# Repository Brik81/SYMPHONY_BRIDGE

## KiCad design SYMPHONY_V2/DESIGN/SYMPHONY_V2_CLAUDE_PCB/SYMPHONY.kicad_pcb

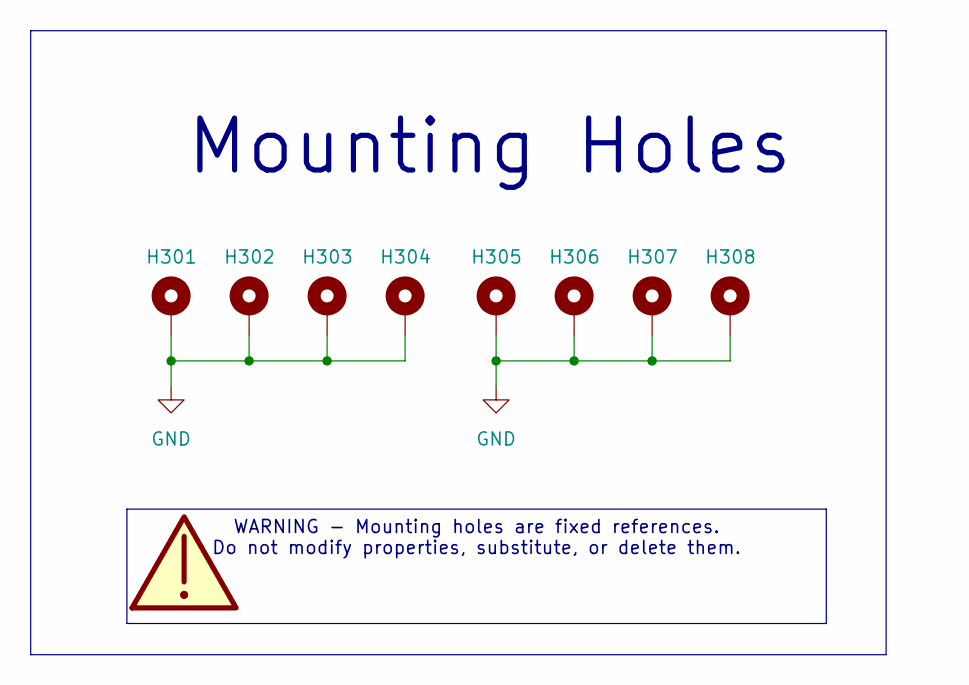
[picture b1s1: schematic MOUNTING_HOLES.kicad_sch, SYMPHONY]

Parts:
H301, H302, H303, H304, H305, H306, H307, H308: MountingHole_Pad; MountingHole_2.2mm_M2_DIN965_Pad

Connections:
GND: H301.1 (1_1), H302.1 (1_1), H303.1 (1_1), H304.1 (1_1), H305.1 (1_1), H306.1 (1_1), H307.1 (1_1), H308.1 (1_1); also elsewhere on the board

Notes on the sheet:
Mounting Holes
WARNING - Mounting holes are fixed references. Do not modify properties, substitute, or delete them.

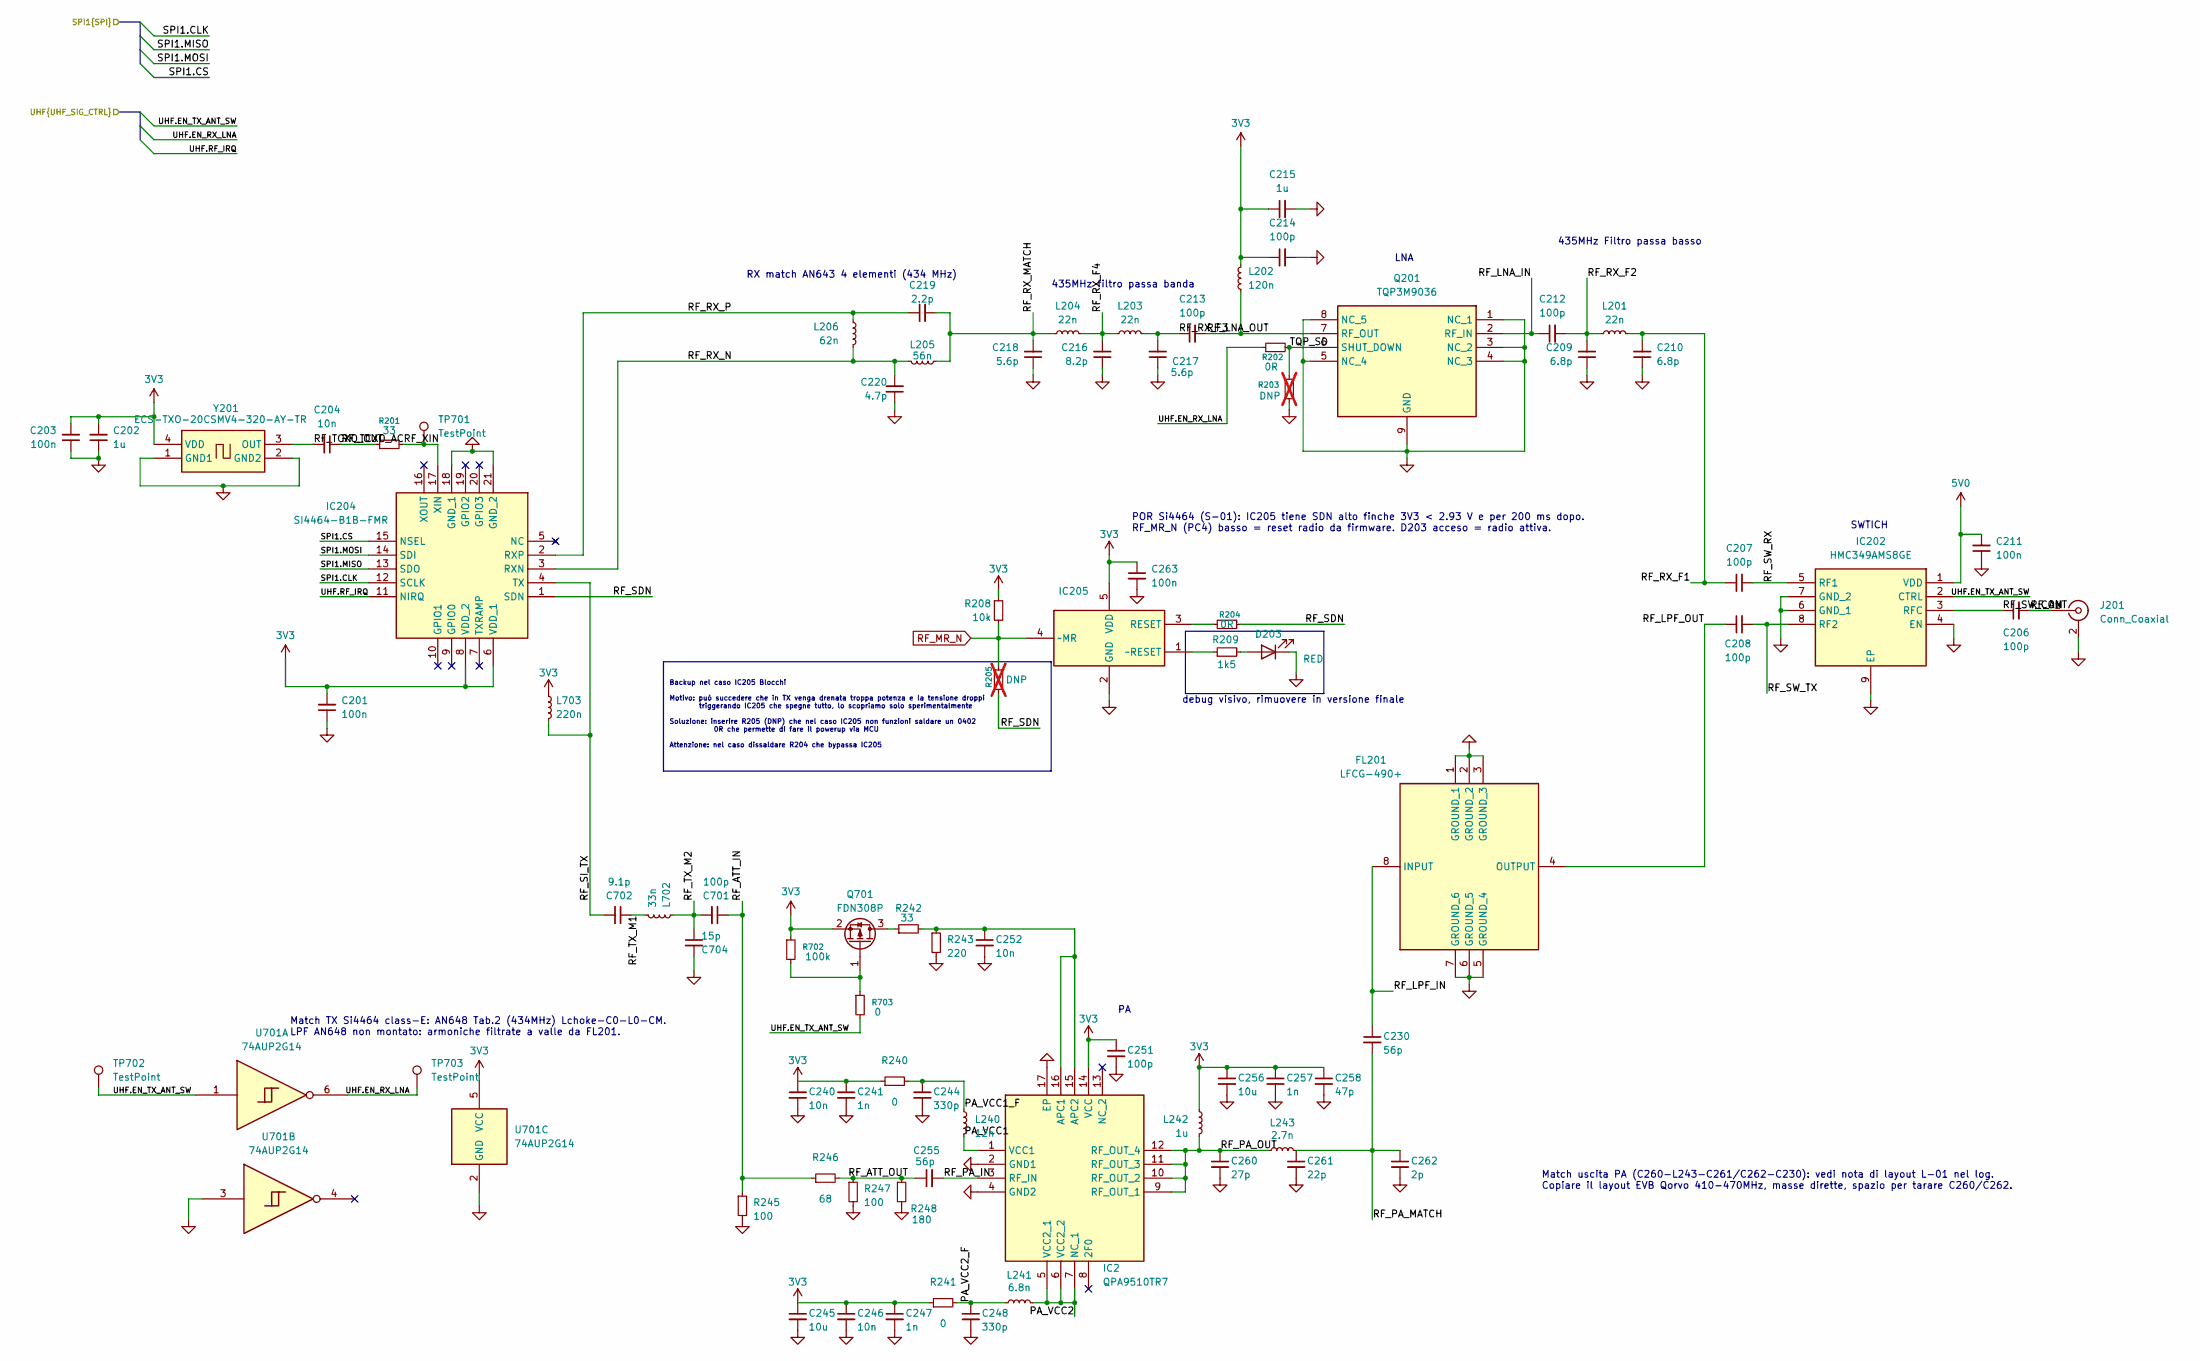
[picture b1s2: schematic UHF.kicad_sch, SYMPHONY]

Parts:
C201, C203, C211, C263: 100n; C_0402_1005Metric; JLCPCB Parts C77014
C202, C215: 1u; C_0402_1005Metric; JLCPCB Parts C77009
C204: 10n; C_0402_1005Metric; JLCPCB Parts C77013
C206, C207, C208, C212, C213, C701: 100p; C_0603_1608Metric; JLCPCB Parts C17308632
C209, C210: 6.8p; C_0805_2012Metric; JLCPCB Parts C464958
C214: 100p; C_0402_1005Metric; JLCPCB Parts C77177
C216: 8.2p; C_0805_2012Metric; JLCPCB Parts C668333
C217, C218: 5.6p; C_0603_1608Metric; JLCPCB Parts C2297617
C219: 2.2p; C_0603_1608Metric; JLCPCB Parts C2179335
C220: 4.7p; C_0805_2012Metric; JLCPCB Parts C5646702
C230, C255: 56p; C_0603_1608Metric; JLCPCB Parts C237591
C240, C246, C252: 10n; C_0402_1005Metric_Pad0.74x0.62mm_HandSolder; JLCPCB Parts C77013
C241, C247, C257: 1n; C_0402_1005Metric_Pad0.74x0.62mm_HandSolder; JLCPCB Parts C76947
C244, C248: 330p; C_0402_1005Metric_Pad0.74x0.62mm_HandSolder; JLCPCB Parts C76965
C245, C256: 10u; C_0805_2012Metric_Pad1.18x1.45mm_HandSolder; JLCPCB Parts C84416
C251: 100p; C_0402_1005Metric_Pad0.74x0.62mm_HandSolder; JLCPCB Parts C77177
C258: 47p; C_0402_1005Metric_Pad0.74x0.62mm_HandSolder; JLCPCB Parts C76970
C260: 27p; C_0603_1608Metric; JLCPCB Parts C2360423
C261: 22p; C_0402_1005Metric; JLCPCB Parts C882567
C262: 2p; C_0402_1005Metric; JLCPCB Parts C161316
C702: 9.1p; C_0402_1005Metric; JLCPCB Parts C497527
C704: 15p; C_0402_1005Metric; JLCPCB Parts C441742
D203: RED; LED_0402_1005Metric; JLCPCB Parts C130719
FL201: LFCG-490+; LFCG490; Mouser Part Number 139-LFCG-490+
IC2: QPA9510TR7; QFN50P300X300X90-17N-D; Manufacturer_Part_Number QPA9510TR7; JLCPCB Parts C52059849
IC202: HMC349AMS8GE; SOP65P490X110-9N; Mouser Part Number 584-HMC349AMS8GE
IC204: SI4464-B1B-FMR; QFN50P400X400X90-21N-D; Mouser Part Number 634-SI4464-B1X-FMR
IC205: TPS3825-33DBVR; SOT95P280X145-5N; Manufacturer_Part_Number TPS3825-33DBVR; JLCPCB Parts C473344
J201: Conn_Coaxial; MMCX_Molex_73415-0961_Horizontal_0.8mm-PCB; JLCPCB Parts C2999837
L201, L203, L204: 22n; L_0805_2012Metric; JLCPCB Parts C2042193
L202: 120n; L_0402_1005Metric_Pad0.77x0.64mm_HandSolder; JLCPCB Parts C113123
L205: 56n; L_0603_1608Metric; JLCPCB Parts C98079
L206: 62n; L_0603_1608Metric; JLCPCB Parts C162649
L240: 12n; L_0603_1608Metric_Pad1.05x0.95mm_HandSolder; JLCPCB Parts C98068
L241: 6.8n; L_0402_1005Metric_Pad0.77x0.64mm_HandSolder; JLCPCB Parts C882467
L242: 1u; L_Taiyo-Yuden_NR-20xx; Manufacturer_Part_Number NRS2012T1R0NGJV; Mouser Part Number 963-NRS2012T1R0NGJV
L243: 2.7n; L_0402_1005Metric; JLCPCB Parts C412269
L702: 33n; L_0805_2012Metric; JLCPCB Parts C1330869
L703: 220n; L_0603_1608Metric; JLCPCB Parts C2046586
Q201: TQP3M9036; SON50P200X200X95-9N-D; Mouser Part Number 772-TQP3M9036
Q701: FDN308P; SOT-23; JLCPCB Parts C7472857
R201: 33; R_0402_1005Metric; JLCPCB Parts C25105
R202, R204: 0R; R_0402_1005Metric; JLCPCB Parts C17168
R203: DNP; R_0402_1005Metric; JLCPCB Parts C71617; not fitted
R205: DNP; R_0402_1005Metric; JLCPCB Parts C17168; not fitted
R208: 10k; R_0402_1005Metric; JLCPCB Parts C71617
R209: 1k5; R_0402_1005Metric; JLCPCB Parts C25867
R240: 0; R_0402_1005Metric_Pad0.72x0.64mm_HandSolder; JLCPCB Parts C17168
R241: 0; R_0603_1608Metric_Pad0.98x0.95mm_HandSolder; JLCPCB Parts C21189
R242: 33; R_0402_1005Metric_Pad0.72x0.64mm_HandSolder; JLCPCB Parts C25105
R243: 220; R_0402_1005Metric_Pad0.72x0.64mm_HandSolder; JLCPCB Parts C25091
R245: 100; R_0603_1608Metric; JLCPCB Parts C22775
R246: 68; R_0603_1608Metric; JLCPCB Parts C27592
R247: 100; R_0402_1005Metric; JLCPCB Parts C25076
R248: 180; R_0402_1005Metric; JLCPCB Parts C38941
R702: 100k; R_0402_1005Metric; JLCPCB Parts C60491
R703: 0; R_0402_1005Metric; JLCPCB Parts C17168
TP701, TP702, TP703: TestPoint; TestPoint_Pad_D1.0mm
U701: 74AUP2G14; SOT-363_SC-70-6; JLCPCB Parts C526337
Y201: ECS-TXO-20CSMV4-320-AY-TR; ECSTXO20CSMV4320AYTR; Manufacturer_Part_Number ECS-TXO-20CSMV4-320-AY-TR; JLCPCB Parts C19858587

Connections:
3V3: C201.2, C202.2, C203.2, C214.1, C215.1, C240.1, C241.1, C245.1, C246.1, C247.1, C251.1, C256.1, C257.1, C258.1, C263.1, IC2.14 (VCC), IC204.6 (VDD_1), IC204.8 (VDD_2), IC205.5 (VDD), L202.2, L242.1, L703.1, Q701.2 (S), R208.1, R240.1, R241.1, R702.1, U701.5 (VCC), Y201.4 (VDD); also elsewhere on the board
5V0: C211.2, IC202.1 (VDD); also elsewhere on the board
/MCU/SPI1.CLK: IC204.12 (SCLK); also elsewhere on the board
/MCU/SPI1.CS: IC204.15 (NSEL); also elsewhere on the board
/MCU/SPI1.MISO: IC204.13 (SDO); also elsewhere on the board
/MCU/SPI1.MOSI: IC204.14 (SDI); also elsewhere on the board
/MCU/UHF.EN_RX_LNA: R202.1, TP703.1 (1_1), U701.6
/MCU/UHF.EN_TX_ANT_SW: IC202.2 (CTRL), R703.2, TP702.1 (1_1), U701.1; also elsewhere on the board
/MCU/UHF.RF_IRQ: IC204.11 (NIRQ); also elsewhere on the board
/UHF/PA_VCC1: IC2.1 (VCC1), L240.2
/UHF/PA_VCC1_F: C244.1, L240.1, R240.2
/UHF/PA_VCC2: IC2.5 (VCC2_1), IC2.6 (VCC2_2), IC2.7 (NC_1), L241.2
/UHF/PA_VCC2_F: C248.1, L241.1, R241.2
/UHF/RF_ANT: C206.2, J201.1 (In)
/UHF/RF_ATT_IN: C701.1, R245.1, R246.1
/UHF/RF_ATT_OUT: C255.1, R246.2, R247.1, R248.1
/UHF/RF_LNA_IN: C212.1, Q201.2 (RF_IN)
/UHF/RF_LNA_OUT: C213.2, L202.1, Q201.7 (RF_OUT)
/UHF/RF_LPF_IN: C230.1, FL201.8 (INPUT)
/UHF/RF_LPF_OUT: C208.1, FL201.4 (OUTPUT)
/UHF/RF_PA_IN: C255.2, IC2.3 (RF_IN)
/UHF/RF_PA_MATCH: C230.2, C261.1, C262.1, L243.2
/UHF/RF_PA_OUT: C260.1, IC2.9 (RF_OUT_1), IC2.10 (RF_OUT_2), IC2.11 (RF_OUT_3), IC2.12 (RF_OUT_4), L242.2, L243.1
/UHF/RF_RX_F1: C207.1, C210.2, L201.2
/UHF/RF_RX_F2: C209.2, C212.2, L201.1
/UHF/RF_RX_F3: C213.1, C217.2, L203.2
/UHF/RF_RX_F4: C216.2, L203.1, L204.2
/UHF/RF_RX_MATCH: C218.2, C219.2, L204.1, L205.2
/UHF/RF_RX_N: C220.2, IC204.3 (RXN), L205.1, L206.2
/UHF/RF_RX_P: C219.1, IC204.2 (RXP), L206.1
/UHF/RF_SDN: IC204.1 (SDN), R204.1, R205.2
/UHF/RF_SI_TX: C702.2, IC204.4 (TX), L703.2
/UHF/RF_SW_COM: C206.1, IC202.3 (RFC)
/UHF/RF_SW_RX: C207.2, IC202.5 (RF1)
/UHF/RF_SW_TX: C208.2, IC202.8 (RF2)
/UHF/RF_TCXO_AC: C204.1, R201.1
/UHF/RF_TCXO_OUT: C204.2, Y201.3 (OUT)
/UHF/RF_TX_M1: C702.1, L702.1
/UHF/RF_TX_M2: C701.2, C704.1, L702.2
/UHF/RF_XIN: IC204.17 (XIN), R201.2, TP701.1 (1_1)
/UHF/TQP_SD: Q201.6 (SHUT_DOWN), R202.2, R203.1
GND: C201.1, C202.1, C203.1, C209.1, C210.1, C211.1, C214.2, C215.2, C216.1, C217.1, C218.1, C220.1, C240.2, C241.2, C244.2, C245.2, C246.2, C247.2, C248.2, C251.2, C252.2, C256.2, C257.2, C258.2, C260.2, C261.2, C262.2, C263.2, C704.2, D203.1 (K), FL201.1 (GROUND_1), FL201.2 (GROUND_2), FL201.3 (GROUND_3), FL201.5 (GROUND_4), FL201.6 (GROUND_5), FL201.7 (GROUND_6), IC2.2 (GND1), IC2.4 (GND2), IC2.17 (EP), IC202.4 (EN), IC202.6 (GND_1), IC202.7 (GND_2), IC202.9 (EP), IC204.18 (GND_1), IC204.21 (GND_2), IC205.2 (GND), J201.2 (Ext), Q201.1 (NC_1), Q201.3 (NC_2), Q201.4 (NC_3), Q201.5 (NC_4), Q201.8 (NC_5), Q201.9 (GND), R203.2, R243.2, R245.2, R247.2, R248.2, U701.2 (GND), U701.3, Y201.1 (GND1), Y201.2 (GND2); also elsewhere on the board
unnamed: D203.2 (A), R209.2
unnamed: C252.1, IC2.15 (APC2), IC2.16 (APC1), R242.2, R243.1
unnamed: IC205.3 (RESET), R204.2
unnamed: IC205.1 (~RESET), R209.1
unnamed: Q701.3 (D), R242.1
unnamed: Q701.1 (G), R702.2, R703.1
RF_MR_N: IC205.4 (~MR), R205.1, R208.2; also elsewhere on the board

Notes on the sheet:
435MHz Filtro passa basso
Match TX Si4464 class-E: AN648 Tab.2 (434MHz) Lchoke-C0-L0-CM. LPF AN648 non montato: armoniche filtrate a valle da FL201.
POR Si4464 (S-01): IC205 tiene SDN alto finche 3V3 < 2.93 V e per 200 ms dopo. RF_MR_N (PC4) basso = reset radio da firmware. D203 acceso = radio attiva.
debug visivo, rimuovere in versione finale
LNA
Backup nel caso IC205 Blocchi Motivo: può succedere che in TX venga drenata troppa potenza e la tensione droppi triggerando IC205 che spegne tutto, lo scopriamo solo sperimentalmente Soluzione: inserire R205 (DNP) che nel caso IC205 non funzioni saldare un 0402 0R che permette di fare il powerup vi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
435MHz filtro passa banda
RX match AN643 4 elementi (434 MHz)
SWTICH
Match uscita PA (C260-L243-C261/C262-C230): vedi nota di layout L-01 nel log. Copiare il layout EVB Qorvo 410-470MHz, masse dirette, spazio per tarare C260/C262.

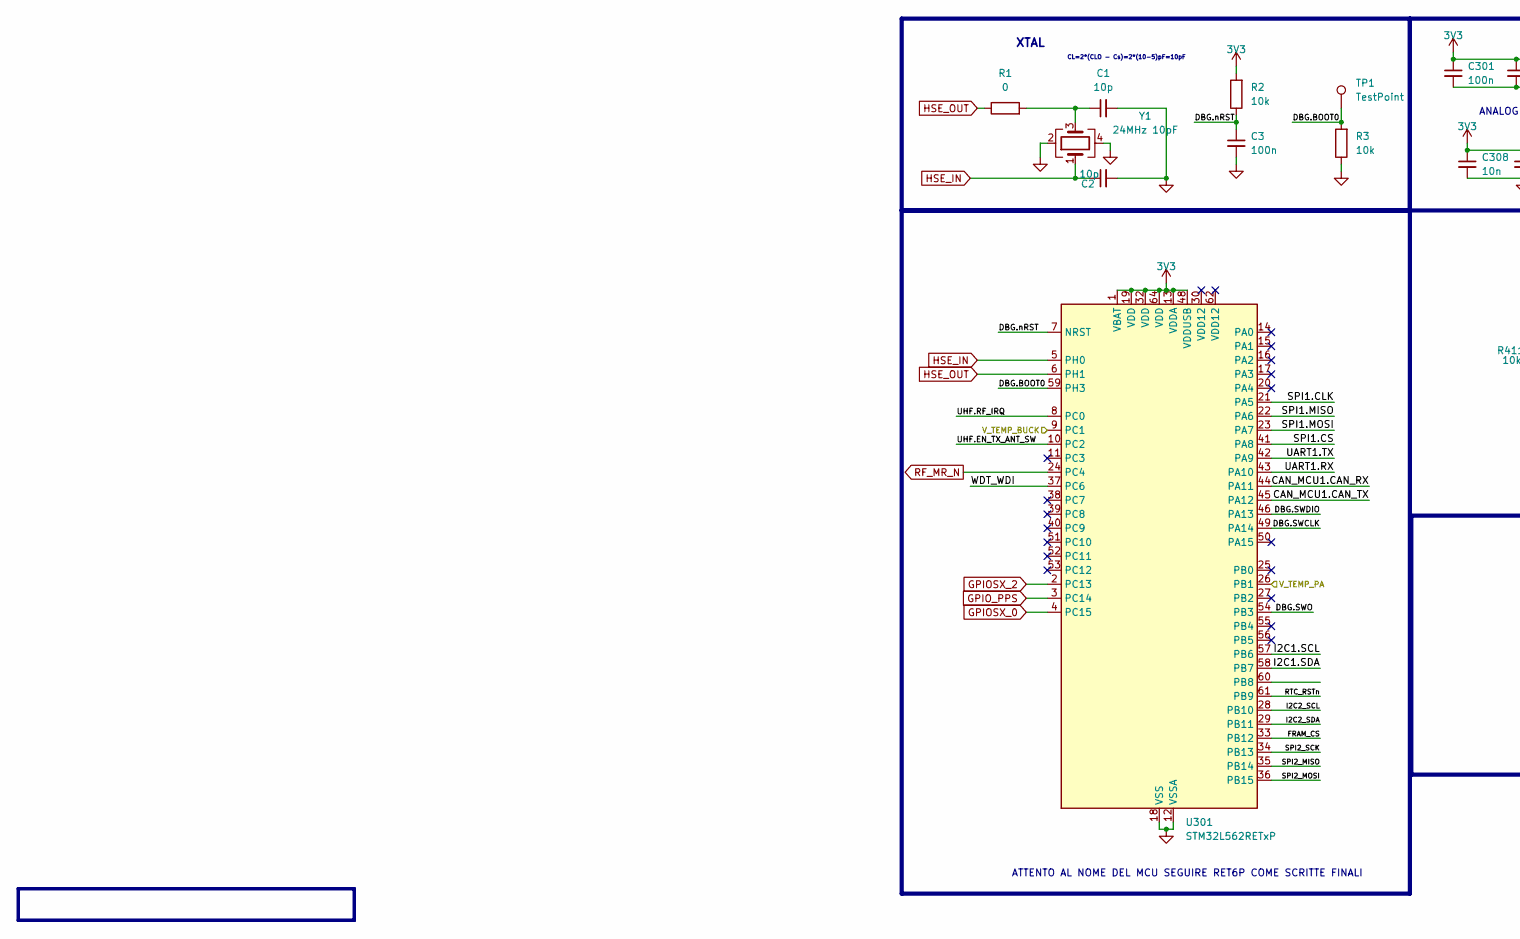
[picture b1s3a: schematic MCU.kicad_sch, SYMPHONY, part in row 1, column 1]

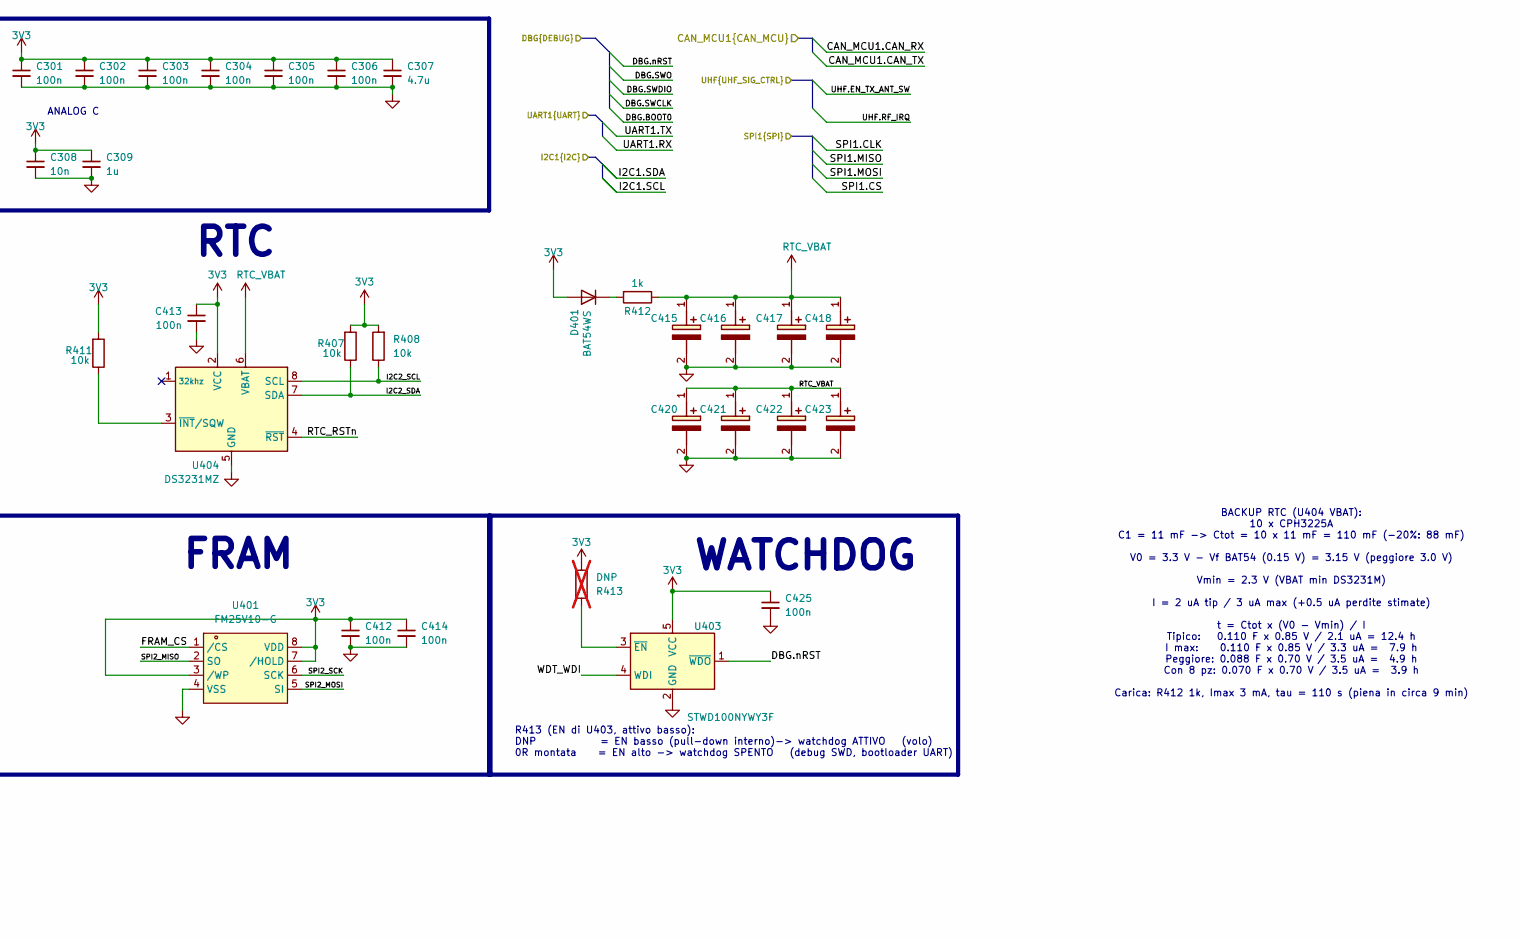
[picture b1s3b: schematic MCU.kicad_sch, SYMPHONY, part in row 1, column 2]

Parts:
C1, C2: 10p; C_0402_1005Metric; JLCPCB Parts C76946
C3, C425: 100n; C_0402_1005Metric; JLCPCB Parts C1525
C301, C302, C303, C304, C305, C306, C412, C413, C414: 100n; C_0402_1005Metric_Pad0.74x0.62mm_HandSolder; JLCPCB Parts C1525
C307: 4.7u; C_0603_1608Metric_Pad1.08x0.95mm_HandSolder; JLCPCB Parts C19666
C308: 10n; C_0402_1005Metric_Pad0.74x0.62mm_HandSolder; JLCPCB Parts C1524
C309: 1u; C_0402_1005Metric_Pad0.74x0.62mm_HandSolder; JLCPCB Parts C14445
C415, C416, C417, C418, C420, C421, C422, C423: CPH3225A; Mouser Part Number 628-CPH3225A
D401: BAT54WS; D_SOD-323; JLCPCB Parts C124205
R1: 0; R_0402_1005Metric_Pad0.72x0.64mm_HandSolder; JLCPCB Parts C17168
R2, R3, R407, R408, R411: 10k; R_0402_1005Metric_Pad0.72x0.64mm_HandSolder; JLCPCB Parts C71617
R412: 1k; R_0402_1005Metric; JLCPCB Parts C11702
R413: DNP; R_0402_1005Metric; JLCPCB Parts C17168; not fitted
TP1: TestPoint; TestPoint_Pad_D1.0mm
U301: STM32L562RETxP; LQFP-64_10x10mm_P0.5mm; JLCPCB Parts C1236664
U401: FM25V10-G; SOIC127P602X173-8N; JLCPCB Parts C44173
U403: STWD100NYWY3F; SOT95P280X145-5N; Manufacturer_Part_Number STWD100NYWY3F; JLCPCB Parts C46043
U404: DS3231MZ; SOIC-8_3.9x4.9mm_P1.27mm; JLCPCB Parts C107410
Y1: 24MHz 10pF; Crystal_SMD_3225-4Pin_3.2x2.5mm; JLCPCB Parts C70583

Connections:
3V3: C301.1, C302.1, C303.1, C304.1, C305.1, C306.1, C307.1, C308.1, C309.1, C412.1, C413.1, C414.1, C425.1, D401.2 (A), R2.2, R407.2, R408.2, R411.2, R413.2, U301.1 (VBAT), U301.13 (VDDA), U301.19 (VDD), U301.32 (VDD), U301.48 (VDDUSB), U301.64 (VDD), U401.3 (/WP), U401.7 (/HOLD), U401.8 (VDD), U403.5 (VCC), U404.2 (VCC); also elsewhere on the board
/IF/CAN_MCU1.CAN_RX: U301.44 (PA11); also elsewhere on the board
/IF/CAN_MCU1.CAN_TX: U301.45 (PA12); also elsewhere on the board
/IF/DBG.BOOT0: R3.2, TP1.1 (1_1), U301.59 (PH3)
/IF/DBG.SWCLK: U301.49 (PA14); also elsewhere on the board
/IF/DBG.SWDIO: U301.46 (PA13); also elsewhere on the board
/IF/DBG.SWO: U301.54 (PB3); also elsewhere on the board
/IF/DBG.nRST: C3.1, R2.1, U301.7 (NRST), U403.1 (~WDO); also elsewhere on the board
/IF/I2C1.SCL: U301.57 (PB6); also elsewhere on the board
/IF/I2C1.SDA: U301.58 (PB7); also elsewhere on the board
/IF/UART1.RX: U301.43 (PA10); also elsewhere on the board
/IF/UART1.TX: U301.42 (PA9); also elsewhere on the board
/MCU/FRAM_CS: U301.33 (PB12), U401.1 (/CS)
/MCU/I2C2_SCL: R408.1, U301.28 (PB10), U404.8 (SCL)
/MCU/I2C2_SDA: R407.1, U301.29 (PB11), U404.7 (SDA)
/MCU/RTC_RSTn: U301.61 (PB9), U404.4 (~RST)
/MCU/SPI1.CLK: U301.21 (PA5); also elsewhere on the board
/MCU/SPI1.CS: U301.41 (PA8); also elsewhere on the board
/MCU/SPI1.MISO: U301.22 (PA6); also elsewhere on the board
/MCU/SPI1.MOSI: U301.23 (PA7); also elsewhere on the board
/MCU/SPI2_MISO: U301.35 (PB14), U401.2 (SO)
/MCU/SPI2_MOSI: U301.36 (PB15), U401.5 (SI)
/MCU/SPI2_SCK: U301.34 (PB13), U401.6 (SCK)
/MCU/UHF.EN_TX_ANT_SW: U301.10 (PC2); also elsewhere on the board
/MCU/UHF.RF_IRQ: U301.8 (PC0); also elsewhere on the board
/MCU/V_TEMP_BUCK: U301.9 (PC1); also elsewhere on the board
/MCU/V_TEMP_PA: U301.26 (PB1); also elsewhere on the board
/MCU/WDT_WDI: U301.37 (PC6), U403.4 (WDI)
GND: C1.2, C2.2, C3.2, C301.2, C302.2, C303.2, C304.2, C305.2, C306.2, C307.2, C308.2, C309.2, C412.2, C413.2, C414.2, C415.2 (-), C416.2 (-), C417.2 (-), C418.2 (-), C420.2 (-), C421.2 (-), C422.2 (-), C423.2 (-), C425.2, R3.1, U301.12 (VSSA), U301.18 (VSS), U301.31 (VSS), U301.47 (VSS), U301.63 (VSS), U401.4 (VSS), U403.2 (GND), U404.5 (GND), Y1.2, Y1.4; also elsewhere on the board
GPIOSX_0: U301.4 (PC15); also elsewhere on the board
GPIOSX_2: U301.2 (PC13); also elsewhere on the board
GPIO_PPS: U301.3 (PC14); also elsewhere on the board
HSE_IN: C2.1, U301.5 (PH0), Y1.1
HSE_OUT: R1.1, U301.6 (PH1)
unnamed: C1.1, R1.2, Y1.3
unnamed: D401.1 (K), R412.2
unnamed: R413.1, U403.3 (~EN)
unnamed: R411.1, U404.3 (~INT/SQW)
RF_MR_N: U301.24 (PC4); also elsewhere on the board
RTC_VBAT: C415.1 (+), C416.1 (+), C417.1 (+), C418.1 (+), C420.1 (+), C421.1 (+), C422.1 (+), C423.1 (+), R412.1, U404.6 (VBAT); also elsewhere on the board

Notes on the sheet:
R413 (EN di U403, attivo basso): DNP = EN basso (pull-down interno)-> watchdog ATTIVO (volo) 0R montata = EN alto -> watchdog SPENTO (debug SWD, bootloader UART)
ATTENTO AL NOME DEL MCU SEGUIRE RET6P COME SCRITTE FINALI
RTC
ANALOG C
FRAM
WATCHDOG
BACKUP RTC (U404 VBAT): 10 x CPH3225A C1 = 11 mF -> Ctot = 10 x 11 mF = 110 mF (-20%: 88 mF) V0 = 3.3 V - Vf BAT54 (0.15 V) = 3.15 V (peggiore 3.0 V) Vmin = 2.3 V (VBAT min DS3231M) I = 2 uA tip / 3 uA max (+0.5 uA perdite stimate) t = Ctot x (V0 - Vmin) / I Tipico: 0.110 F x 0.85 V / 2.1 uA = 12.4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
XTAL
CL=2*(CLO - Cs)=2*(10-5)pF=10pF

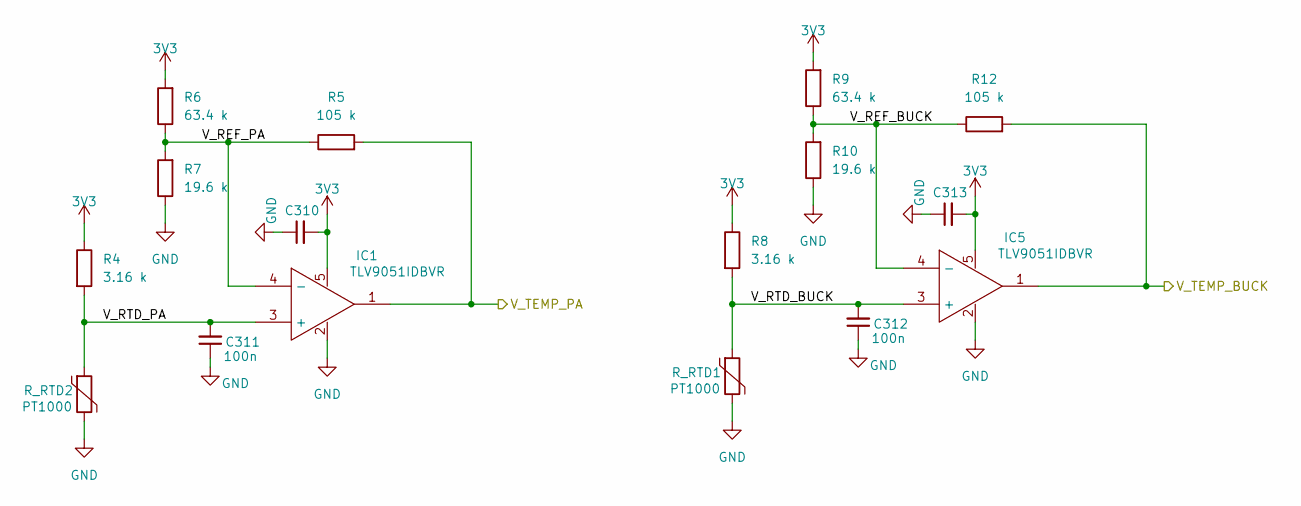
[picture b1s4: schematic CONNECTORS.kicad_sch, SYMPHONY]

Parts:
C310, C311, C312, C313: 100n; C_0402_1005Metric_Pad0.74x0.62mm_HandSolder; JLCPCB Parts C1525
IC1, IC5: TLV9051IDBVR; SOT95P280X145-5N; Mouser Part Number 595-TLV9051IDBVR
R4, R8: 3.16 k; R_0402_1005Metric_Pad0.72x0.64mm_HandSolder; JLCPCB Parts C852759
R5, R12: 105 k; R_0402_1005Metric_Pad0.72x0.64mm_HandSolder; JLCPCB Parts C2984407
R6, R9: 63.4 k; R_0402_1005Metric_Pad0.72x0.64mm_HandSolder; JLCPCB Parts C852877
R7, R10: 19.6 k; R_0402_1005Metric_Pad0.72x0.64mm_HandSolder; JLCPCB Parts C852589
R_RTD1, R_RTD2: PT1000; R_0603_1608Metric_Pad0.98x0.95mm_HandSolder; MPN 32207638

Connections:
3V3: C310.2, C313.2, IC1.5, IC5.5, R4.1, R6.2, R8.1, R9.2; also elsewhere on the board
/MCU/V_TEMP_BUCK: IC5.1, R12.2; also elsewhere on the board
/MCU/V_TEMP_PA: IC1.1, R5.2; also elsewhere on the board
/SENSORS/V_REF_BUCK: IC5.4 (-), R9.1, R10.2, R12.1
/SENSORS/V_REF_PA: IC1.4 (-), R5.1, R6.1, R7.2
/SENSORS/V_RTD_BUCK: C312.2, IC5.3 (+), R8.2, R_RTD1.1
/SENSORS/V_RTD_PA: C311.2, IC1.3 (+), R4.2, R_RTD2.1
GND: C310.1, C311.1, C312.1, C313.1, IC1.2, IC5.2, R7.1, R10.1, R_RTD1.2, R_RTD2.2; also elsewhere on the board

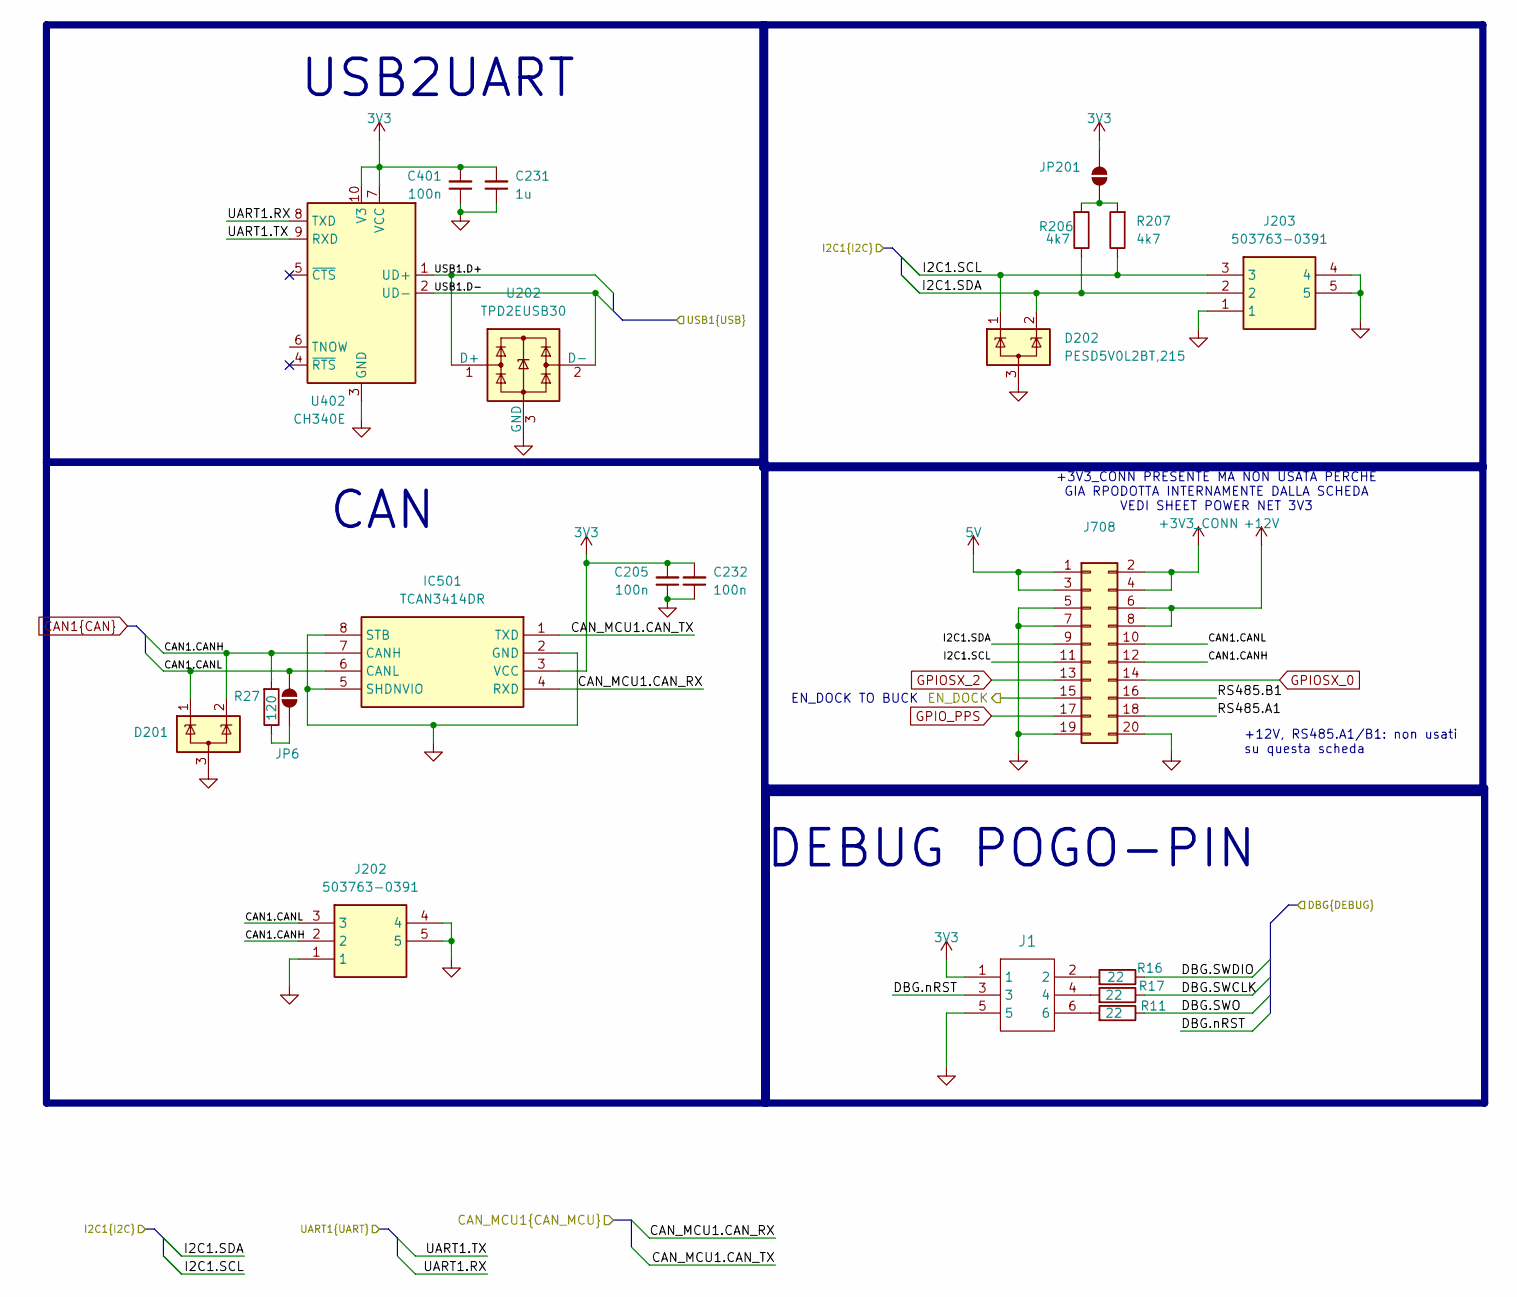
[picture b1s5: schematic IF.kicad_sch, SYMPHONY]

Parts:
C205, C232, C401: 100n; C_0402_1005Metric; JLCPCB Parts C1525
C231: 1u; C_0402_1005Metric; JLCPCB Parts C29266
D201: ESD2CAN24DBZRQ1; SOT-23-3; JLCPCB Parts C5736151
D202: PESD5V0L2BT,215; SOT-23-3; JLCPCB Parts C12324
IC501: TCAN3414DR; SOIC127P600X175-8N; Mouser Part Number 595-TCAN3414DR
J1: TC2030-IDC-pogo-pin; CONN_TC2030-IDC_TGC
J202, J203: 503763-0391; 5037630391; Mouser Part Number 538-503763-0391
J708: FSI-110-03-G-D-AB; FSI11003GDAB_Mating; JLCPCB Parts C7278162
JP6, JP201: SolderJumper_2_Open; SolderJumper-2_P1.3mm_Open_RoundedPad1.0x1.5mm
R11, R16, R17: 22; R_0402_1005Metric_Pad0.72x0.64mm_HandSolder; JLCPCB Parts C25092
R27: 120; R_0805_2012Metric; JLCPCB Parts C17437
R206, R207: 4k7; R_0402_1005Metric_Pad0.72x0.64mm_HandSolder; JLCPCB Parts C25900
U202: TPD2EUSB30; Texas_DRT-3; JLCPCB Parts C97502
U402: CH340E; MSOP-10_3x3mm_P0.5mm; JLCPCB Parts C99652

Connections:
3V3: C205.2, C231.2, C232.2, C401.2, IC501.3 (VCC), J1.1, JP201.2 (B), U402.7 (VCC), U402.10 (V3); also elsewhere on the board
5V: J708.1, J708.3; also elsewhere on the board
+3V3_CONN: J708.2, J708.4
+12V: J708.6, J708.8
/IF/CAN_MCU1.CAN_RX: IC501.4 (RXD); also elsewhere on the board
/IF/CAN_MCU1.CAN_TX: IC501.1 (TXD); also elsewhere on the board
/IF/DBG.SWCLK: R17.1; also elsewhere on the board
/IF/DBG.SWDIO: R16.1; also elsewhere on the board
/IF/DBG.SWO: R11.1; also elsewhere on the board
/IF/DBG.nRST: J1.3; also elsewhere on the board
/IF/EN_DOCK: J708.15; also elsewhere on the board
/IF/I2C1.SCL: D202.1 (K), J203.3, J708.11, R207.1; also elsewhere on the board
/IF/I2C1.SDA: D202.2 (K), J203.2, J708.9, R206.1; also elsewhere on the board
/IF/RS485.A1: J708.18
/IF/RS485.B1: J708.16
/IF/UART1.RX: U402.8 (TXD); also elsewhere on the board
/IF/UART1.TX: U402.9 (RXD); also elsewhere on the board
/IF/USB1.D+: U202.1 (D+), U402.1 (UD+); also elsewhere on the board
/IF/USB1.D-: U202.2 (D-), U402.2 (UD-); also elsewhere on the board
CAN1.CANH: D201.2 (K), IC501.7 (CANH), J202.2, J708.12, R27.2
CAN1.CANL: D201.1 (K), IC501.6 (CANL), J202.3, J708.10, JP6.2 (B)
GND: C205.1, C231.1, C232.1, C401.1, D201.3 (A), D202.3 (A), IC501.2 (GND), IC501.5 (SHDNVIO), IC501.8 (STB), J1.5, J202.1, J202.4, J202.5, J203.1, J203.4, J203.5, J708.5, J708.7, J708.19, J708.20, U202.3 (GND), U402.3 (GND); also elsewhere on the board
GPIOSX_0: J708.14; also elsewhere on the board
GPIOSX_2: J708.13; also elsewhere on the board
GPIO_PPS: J708.17; also elsewhere on the board
unnamed: J1.2, R16.2
unnamed: J1.4, R17.2
unnamed: J1.6, R11.2
unnamed: JP6.1 (A), R27.1
unnamed: JP201.1 (A), R206.2, R207.2

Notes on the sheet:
EN_DOCK TO BUCK
USB2UART
+3V3_CONN PRESENTE MA NON USATA PERCHE GIA RPODOTTA INTERNAMENTE DALLA SCHEDA VEDI SHEET POWER NET 3V3
CAN
DEBUG POGO-PIN
+12V, RS485.A1/B1: non usati su questa scheda

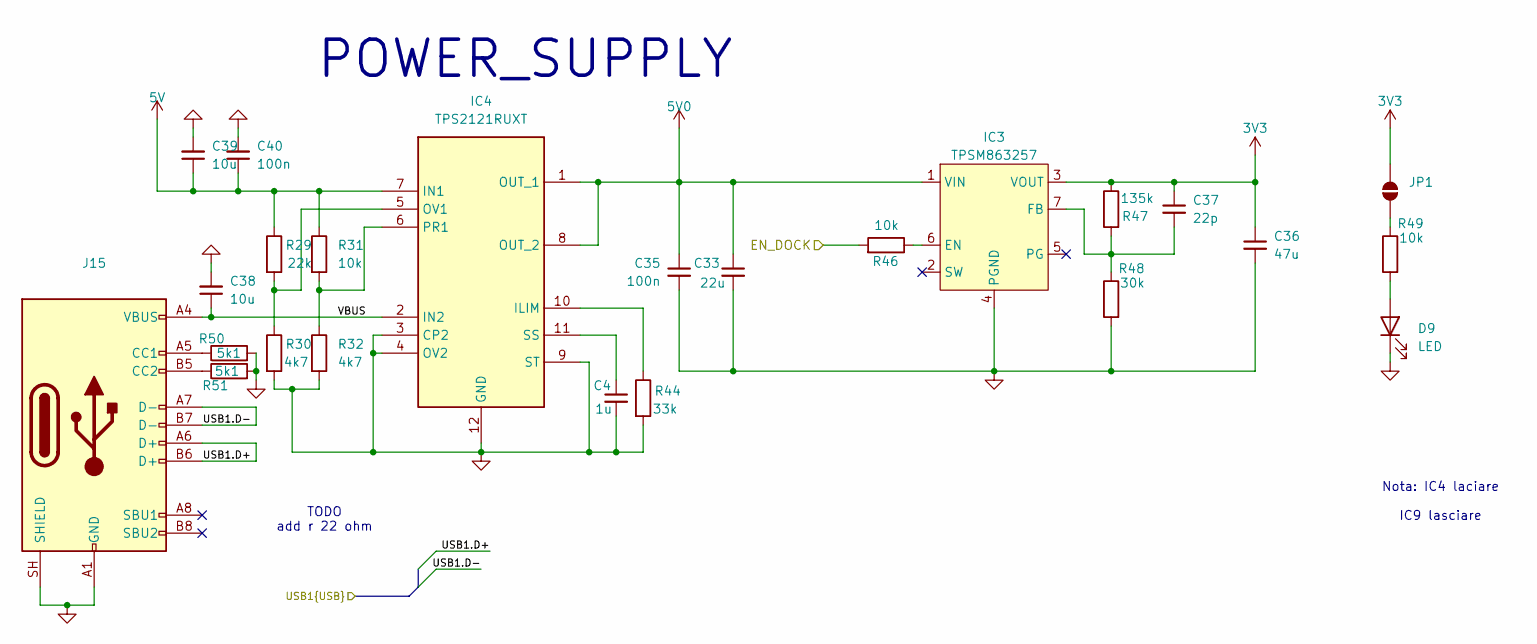
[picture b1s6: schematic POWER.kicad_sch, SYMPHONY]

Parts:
C4: 1u; C_0603_1608Metric; JLCPCB Parts C29936
C33: 22u; C_0805_2012Metric; JLCPCB Parts C45783
C35, C40: 100n; C_0402_1005Metric; JLCPCB Parts C1525
C36: 47u; C_1210_3225Metric; JLCPCB Parts C84494
C37: 22p; C_0402_1005Metric_Pad0.74x0.62mm_HandSolder; JLCPCB Parts C2191676
C38: 10u; C_0805_2012Metric; JLCPCB Parts C15850
C39: 10u; C_0402_1005Metric; JLCPCB Parts C315248
D9: LED; LED_0402_1005Metric; JLCPCB Parts C130723
IC3: TPSM863257; JLCPCB Parts C19190416
IC4: TPS2121RUXT; Mouser Part Number 595-TPS2121RUXT
J15: USB_C_Receptacle_USB2.0_16P; USB_C_Receptacle_GCT_USB4105-xx-A_16P_TopMnt_Horizontal; JLCPCB Parts C393939
JP1: SolderJumper_2_Open; SolderJumper-2_P1.3mm_Open_RoundedPad1.0x1.5mm
R29: 22k; R_0402_1005Metric; JLCPCB Parts C25547
R30, R32: 4k7; R_0402_1005Metric; JLCPCB Parts C25900
R31: 10k; R_0402_1005Metric; JLCPCB Parts C71617
R44: 33k; R_0402_1005Metric; JLCPCB Parts C25779
R46, R49: 10k; R_0402_1005Metric_Pad0.72x0.64mm_HandSolder; JLCPCB Parts C71617
R47: 135k; R_0402_1005Metric_Pad0.72x0.64mm_HandSolder; JLCPCB Parts C2515705
R48: 30k; R_0402_1005Metric_Pad0.72x0.64mm_HandSolder; JLCPCB Parts C100362
R50, R51: 5k1; R_0402_1005Metric; JLCPCB Parts C25905

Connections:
3V3: C36.1, C37.1, IC3.3 (VOUT), JP1.2 (B), R47.1; also elsewhere on the board
5V: C39.1, C40.1, IC4.7 (IN1), R29.1, R31.1; also elsewhere on the board
5V0: C33.1, C35.1, IC3.1 (VIN), IC4.1 (OUT_1), IC4.8 (OUT_2); also elsewhere on the board
/IF/EN_DOCK: R46.2; also elsewhere on the board
/IF/USB1.D+: J15.A6 (D+), J15.B6 (D+); also elsewhere on the board
/IF/USB1.D-: J15.A7 (D-), J15.B7 (D-); also elsewhere on the board
/POWER/VBUS: C38.1, IC4.2 (IN2), J15.A4 (VBUS), J15.A9 (VBUS), J15.B4 (VBUS), J15.B9 (VBUS)
GND: C4.2, C33.2, C35.2, C36.2, C38.2, C39.2, C40.2, D9.1 (K), IC3.4 (PGND), IC4.3 (CP2), IC4.4 (OV2), IC4.9 (ST), IC4.12 (GND), J15.A1 (GND), J15.A12 (GND), J15.B1 (GND), J15.B12 (GND), J15.SH (SHIELD), R30.2, R32.2, R44.2, R48.2, R50.2, R51.2; also elsewhere on the board
unnamed: D9.2 (A), R49.2
unnamed: IC3.6 (EN), R46.1
unnamed: C37.2, IC3.7 (FB), R47.2, R48.1
unnamed: IC4.10 (ILIM), R44.1
unnamed: IC4.5 (OV1), R29.2, R30.1
unnamed: IC4.6 (PR1), R31.2, R32.1
unnamed: C4.1, IC4.11 (SS)
unnamed: J15.A5 (CC1), R50.1
unnamed: J15.B5 (CC2), R51.1
unnamed: JP1.1 (A), R49.1

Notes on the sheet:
TODO add r 22 ohm
POWER_SUPPLY
Nota: IC4 laciare IC9 lasciare
